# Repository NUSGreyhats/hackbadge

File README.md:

# HackBadge

Badge designed for HackBash 2025.

## Set Up
Clone the repositories with submodules:
```bash
git clone --recurse-submodules https://github.com/NUSGreyhats/hackbadge.git
```

If you have already cloned the repository, initialize the submodules by running: `git submodule update --init --recursive`.

## Features
=== INSERT PCB IMAGE HERE ===

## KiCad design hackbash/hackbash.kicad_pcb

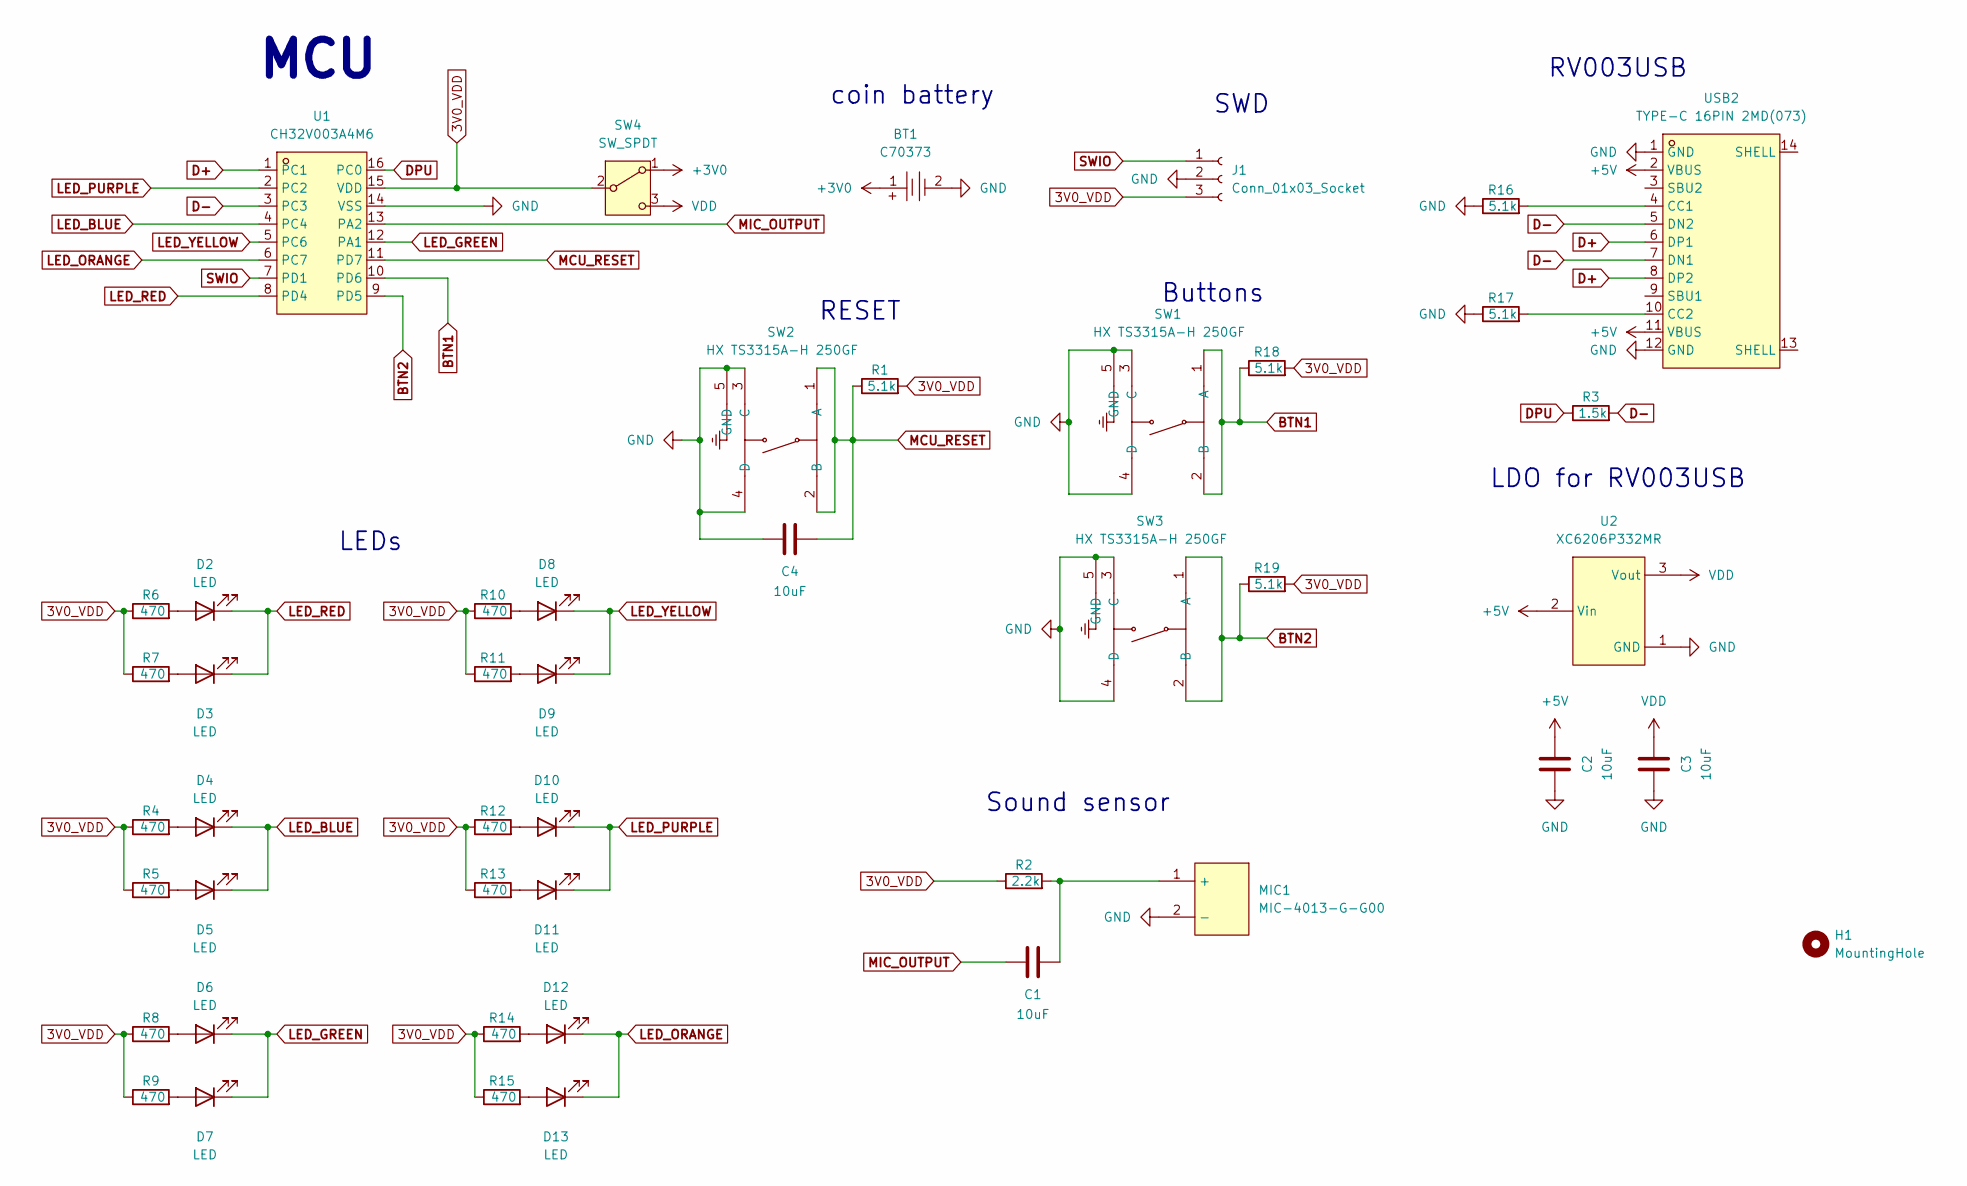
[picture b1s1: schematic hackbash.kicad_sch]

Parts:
BT1: C70373; BAT-SMD_CR2032-3V; LCSC Part C70373
C1, C2, C3, C4: 10uF; C_0805_2012Metric_Pad1.18x1.45mm_HandSolder
D2, D3, D4, D5, D6, D7, D8, D9, D10, D11, D12, D13: LED; LED_0805_2012Metric_Pad1.15x1.40mm_HandSolder
H1: MountingHole; MountingHole_3.2mm_M3_DIN965_Pad
J1: Conn_01x03_Socket; PinSocket_1x03_P2.54mm_Vertical_SMD_Pin1Right
MIC1: MIC-4013-G-G00; MIC-SMD_BD4.0-4013_SMDA; LCSC Part C42371093
R1, R16, R17, R18, R19: 5.1k; R_0805_2012Metric_Pad1.20x1.40mm_HandSolder
R2: 2.2k; R_0805_2012Metric_Pad1.20x1.40mm_HandSolder
R3: 1.5k; R_0805_2012Metric_Pad1.20x1.40mm_HandSolder
R4, R5, R6, R7, R8, R9, R10, R11, R12, R13, R14, R15: 470; R_0805_2012Metric_Pad1.20x1.40mm_HandSolder
SW1, SW2, SW3: HX TS3315A-H 250GF; SW-SMD_4P-L3.4-W3.4-P2.00-LS4.0_TS3315A160GF; LCSC Part C5143623
SW4: SW_SPDT; SW-SMD_SK-01A-H1.5
U1: CH32V003A4M6; SOIC-16_L9.9-W3.9-P1.27-LS6.0-BL; LCSC Part C5346357
U2: XC6206P332MR; SOT-23-3_L2.9-W1.6-P1.90-LS2.8-BR; LCSC Part C5446
USB2: TYPE-C 16PIN 2MD(073); USB-C-SMD_TYPE-C-6PIN-2MD-073; LCSC Part C2765186

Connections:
3V0_VDD: J1.3, R1.2, R2.1, R4.1, R5.1, R6.1, R7.1, R8.1, R9.1, R10.1, R11.1, R12.1, R13.1, R14.1, R15.1, R18.2, R19.2, SW4.2 (B), U1.15 (VDD)
+3V0: BT1.1, SW4.1 (A)
+5V: C2.2, U2.2 (Vin), USB2.2 (VBUS), USB2.11 (VBUS)
BTN1: R18.1, SW1.1 (A), SW1.2 (B), U1.10 (PD6)
BTN2: R19.1, SW3.1 (A), SW3.2 (B), U1.9 (PD5)
D+: U1.1 (PC1), USB2.6 (DP1), USB2.8 (DP2)
D-: R3.2, U1.3 (PC3), USB2.5 (DN2), USB2.7 (DN1)
DPU: R3.1, U1.16 (PC0)
GND: BT1.2, C2.1, C3.1, C4.1, J1.2, MIC1.2 (-), R16.1, R17.1, SW1.3 (C), SW1.4 (D), SW1.5 (GND), SW2.3 (C), SW2.4 (D), SW2.5 (GND), SW3.3 (C), SW3.4 (D), SW3.5 (GND), U1.14 (VSS), U2.1 (GND), USB2.1 (GND), USB2.12 (GND); also elsewhere on the board
LED_BLUE: D4.1 (K), D5.1 (K), U1.4 (PC4)
LED_GREEN: D6.1 (K), D7.1 (K), U1.12 (PA1)
LED_ORANGE: D12.1 (K), D13.1 (K), U1.6 (PC7)
LED_PURPLE: D10.1 (K), D11.1 (K), U1.2 (PC2)
LED_RED: D2.1 (K), D3.1 (K), U1.8 (PD4)
LED_YELLOW: D8.1 (K), D9.1 (K), U1.5 (PC6)
MCU_RESET: C4.2, R1.1, SW2.1 (A), SW2.2 (B), U1.11 (PD7)
MIC_OUTPUT: C1.1, U1.13 (PA2)
unnamed: D2.2 (A), R6.2
unnamed: D3.2 (A), R7.2
unnamed: D4.2 (A), R4.2
unnamed: D5.2 (A), R5.2
unnamed: D6.2 (A), R8.2
unnamed: D7.2 (A), R9.2
unnamed: D8.2 (A), R10.2
unnamed: D9.2 (A), R11.2
unnamed: D10.2 (A), R12.2
unnamed: D11.2 (A), R13.2
unnamed: D12.2 (A), R14.2
unnamed: D13.2 (A), R15.2
unnamed 29: C1.2, MIC1.1 (+), R2.2; also elsewhere on the board
unnamed: R16.2, USB2.4 (CC1)
unnamed: R17.2, USB2.10 (CC2)
SWIO: J1.1, U1.7 (PD1)
VDD: C3.2, SW4.3 (C), U2.3 (Vout)

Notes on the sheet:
LDO for RV003USB
SWD
Sound sensor
LEDs
RV003USB
coin battery
MCU
RESET
Buttons

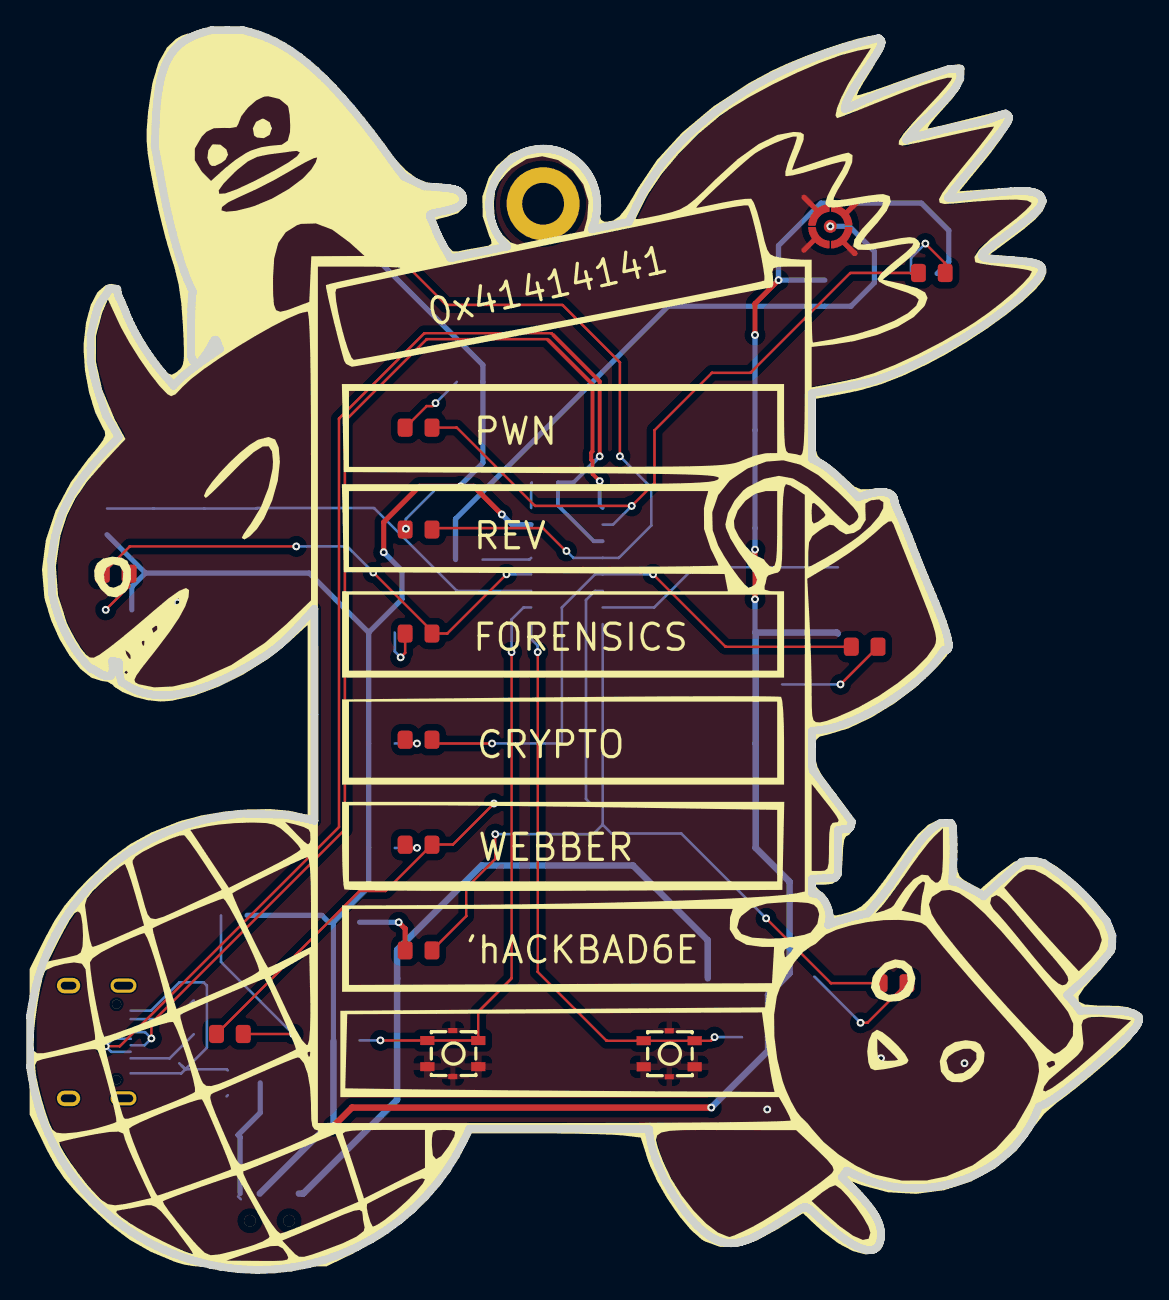
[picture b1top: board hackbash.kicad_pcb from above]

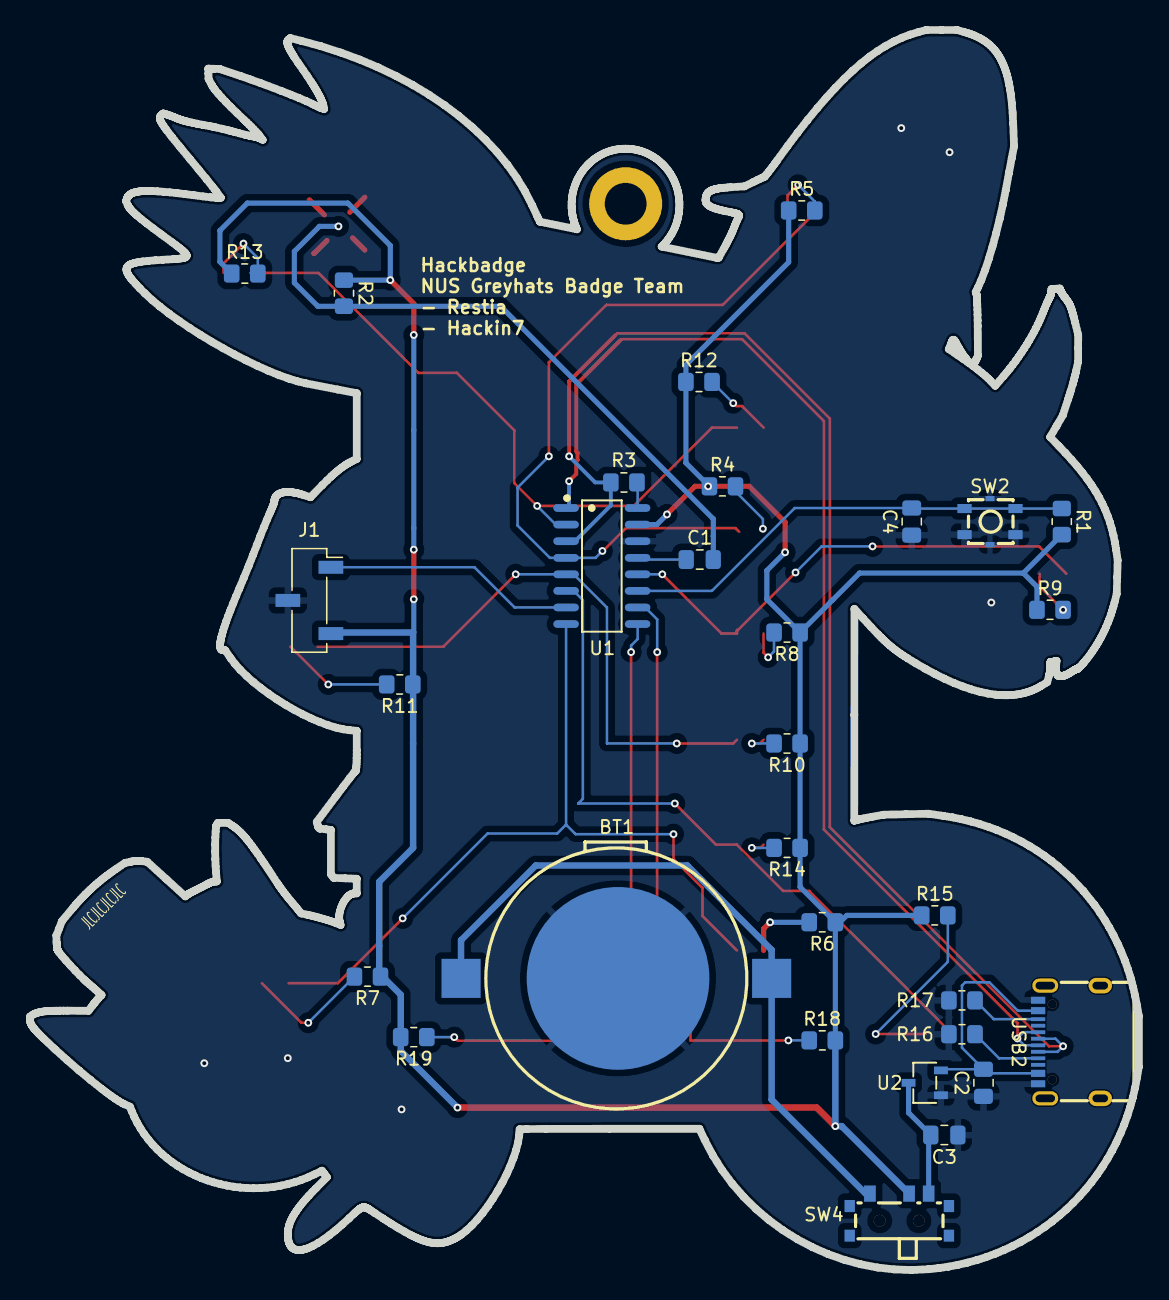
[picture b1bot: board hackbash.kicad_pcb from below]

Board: 2 copper layers, 85.0 x 95.0 mm, 46 parts (30 on the bottom side), 34 nets.

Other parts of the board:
MIC: MIC-4013-G-G00; MIC-SMD_BD4.0-4013_SMDA

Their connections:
GND: MIC.2 (-); also elsewhere on the board
unnamed 29: MIC.1 (+); also elsewhere on the board

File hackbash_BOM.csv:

"Reference","Value","Datasheet","Footprint","Qty","DNP"
"BT1","C70373","https://lcsc.com/product-detail/Battery-Holders-Clips-Contac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","easyeda2kicad:BAT-SMD_CR2032-3V","1",""
"C1,C2,C3,C4","10uF","~","Capacitor_SMD:C_0805_2012Metric_Pad1.18x1.45mm_HandSolder","4",""
"D2,D3,D4,D5,D6,D7,D8,D9,D10,D11,D12,D13","LED","~","LED_SMD:LED_0805_2012Metric_Pad1.15x1.40mm_HandSolder","12",""
"J1","Conn_01x03_Socket","~","Connector_PinSocket_2.54mm:PinSocket_1x03_P2.54mm_Vertical_SMD_Pin1Right","1",""
"MIC1","MIC-4013-G-G00","","easyeda2kicad:MIC-SMD_BD4.0-4013_SMDA","1",""
"R1,R16,R17,R18,R19","5.1k","~","Resistor_SMD:R_0805_2012Metric_Pad1.20x1.40mm_HandSolder","5",""
"R2","2.2k","~","Resistor_SMD:R_0805_2012Metric_Pad1.20x1.40mm_HandSolder","1",""
"R3","1.5k","~","Resistor_SMD:R_0805_2012Metric_Pad1.20x1.40mm_HandSolder","1",""
"R4,R5,R6,R7,R8,R9,R10,R11,R12,R13,R14,R15","470","~","Resistor_SMD:R_0805_2012Metric_Pad1.20x1.40mm_HandSolder","12",""
"SW1,SW2,SW3","HX TS3315A-H 250GF","","easyeda2kicad:SW-SMD_4P-L3.4-W3.4-P2.00-LS4.0_TS3315A160GF","3",""
"SW4","SW_SPDT","~","easyeda2kicad:SW-SMD_SK-01A-H1.5","1",""
"U1","CH32V003A4M6","","easyeda2kicad:SOIC-16_L9.9-W3.9-P1.27-LS6.0-BL","1",""
"U2","XC6206P332MR","https://lcsc.com/product-detail/Low-Dropout-Regulators-LDO_X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","easyeda2kicad:SOT-23-3_L2.9-W1.6-P1.90-LS2.8-BR","1",""
"USB2","TYPE-C 16PIN 2MD(073)","","easyeda2kicad:USB-C-SMD_TYPE-C-6PIN-2MD-073","1",""

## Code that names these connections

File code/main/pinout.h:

// LED pins for raw value display
#define LED_PURPLE   PD3 //        T1CH4_1                          T2CH2, T2CH2_2/
#define LED_RED      PD2 //                   T1CH1_2   T1CH2N_3,          T2CH3_1
#define LED_ORANGE   PC7 //        T1CH2_1              T1CH2_3            T2CH2_3  
#define LED_YELLOW   PC6 //        T1CH1_1,             T1CH3N_3 
#define LED_GREEN    PC5 //                             T1CH3_3      T1ETR, T2CH1ETR(1)_1,
#define LED_BLUE     PC4 // T1CH4, T1CH2N_1 / T1CH4_2 / T1CH1_3

#define funPinModeClear(pin, no) { GpioOf(pin)->CFGLR &= ~((GPIO_Speed_10MHz | GPIO_CNF_OUT_PP_AF)<<(4*no)); }

#define BTN_RIGHT    PD0
#define BTN_LEFT     PC2

#define MIC PA2

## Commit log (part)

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2025-10-02 latest
2025-10-05 pcb design in kicad done
2025-10-15 chore: cleanup repo
2025-10-15 feat: art design
2025-10-17 touched up and converted to easyeda project
2025-10-20 final work sent for fabrication
2025-12-08 added code base
2025-12-24 feat: simple led cycle
2025-12-24 feat: buttons blinky
2025-12-24 feat: set up submodule
2025-12-24 feat: blue led pwm
2025-12-24 feat: timer pwm red led also
2025-12-24 feat: purple LED PWM
2025-12-24 feat: Timer PWM stuff allows all pins to be on
2025-12-24 feat: cycle through LEDs
2025-12-25 feat: somewhat functional pwm
2025-12-25 feat: functioning timer_pwm code to reduce LED brightness?
2025-12-25 chore: pwm some refactoring
2025-12-25 feat: enable for timer 2
2025-12-25 feat: code reorganisation
2025-12-25 feat: breathing good
2025-12-25 feat: pwm leds audio volume
2025-12-25 feat: breathing led pwm
2025-12-25 feat: mvp code working somewhat
2025-12-25 feat: base splitting up code
2025-12-25 feat: code blinky refactoring
2025-12-25 feat: button interrupts poc
2025-12-25 feat: 2 button interrupts
2025-12-25 feat: button interrupts header file
2025-12-25 change main mode to button interrupts
2025-12-25 feat: blinky modes
2025-12-25 feat: blinky patterns
2025-12-25 feat: some rough ctf mode
2025-12-25 feat: basic ctf mode
2025-12-25 feat: rough ctf mode
2025-12-25 feat: copy flash example
2025-12-25 chore: refactor into functions
2025-12-25 feat: this is actually bitmasking wtf
2025-12-25 feat: badgestate flash writing
2025-12-25 feat: badge_state refactoring
2025-12-25 feat: selective unlocks
2025-12-25 feat: fix ctf mode button
2025-12-25 feat: more robust ctf unlock system
2025-12-25 feat: badge unlocks
2025-12-25 feat: ctf dimmer lights
2025-12-28 feat: add README
2025-12-28 fix: comparison btwn ptr and int
2025-12-28 fix: add missing return
2025-12-29 fix: correctly use placeholder vals for buffer
2025-12-29 refactor: remove unused vars
2025-12-29 refactor: makefile
2025-12-29 refactor: add back flash in makefile
2025-12-29 refactor: cast ticks_from_ms to reduce warnings
2026-01-20 everything besides envrionment, unable to compile
2026-01-20 makefile_old added
2026-01-20 fix: led not working bug on mode switching of leds
2026-01-20 feat: crypto blinky space optimisation (thx sayo for identifying fp)
2026-01-20 Fix fade pulsing all leds at max brightness in every cycle
2026-01-22 fix: fade pulsing all leds at max brightness in every cycle
2026-01-22 refactor: rework mic to properly sample and show correct sound level
2026-01-22 feat: led gatekeeping
2026-01-22 feat: mvp mvp firmware done, now left optimising
2026-01-22 feat: mvp firmware
2026-01-22 feat: led sparkle mode - mvp 2
2026-01-22 feat: change changeMode method
2026-01-23 feat: move debug printing to a own function
2026-01-23 refactor: disable all debug printing in main
2026-01-23 refactor: replace string references with cha
2026-01-23 chore: get rid of some warnings
2026-01-23 feat: sleep mode?????? It works nao????
2026-01-23 feat: balance out timings and code on lower clock speed
